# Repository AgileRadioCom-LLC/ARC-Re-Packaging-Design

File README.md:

# RPKG
Repo for ArcSynerCom RPKG Files
# ARC-Re-Packaging-Design

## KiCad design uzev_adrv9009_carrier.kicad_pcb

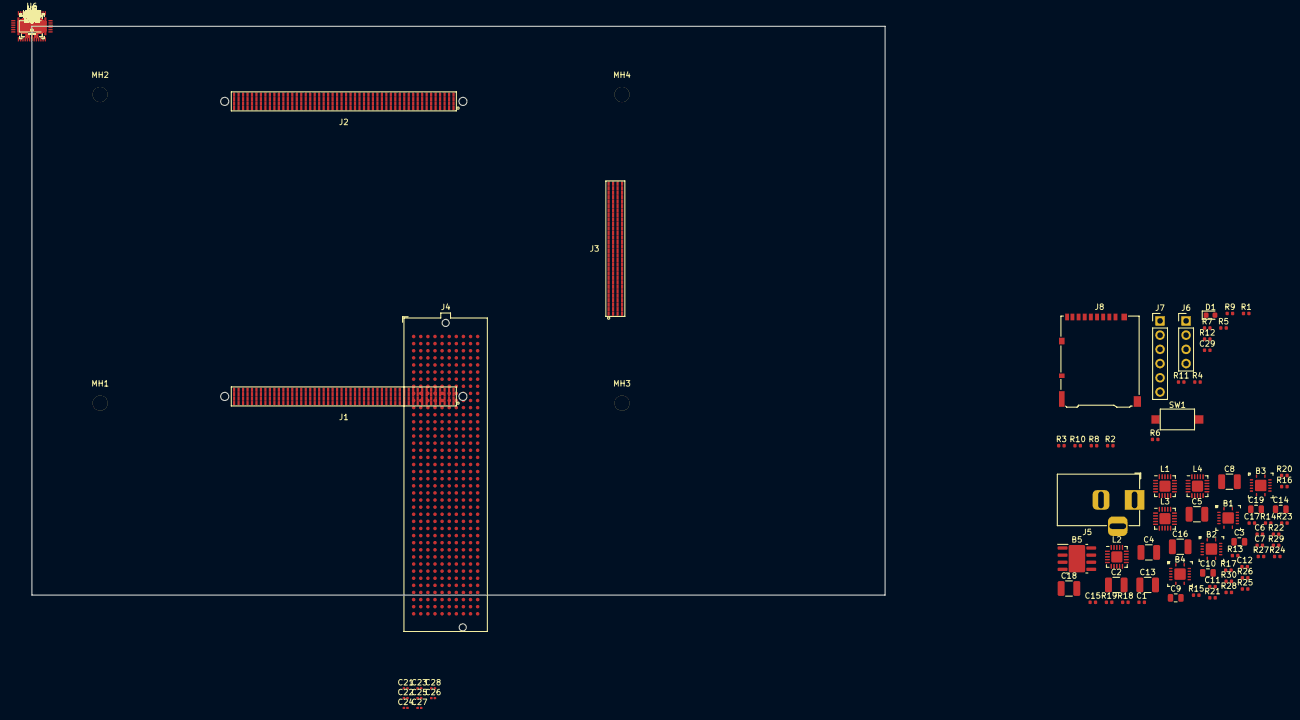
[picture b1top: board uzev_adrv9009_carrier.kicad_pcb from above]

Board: 8 copper layers, 152.4 x 101.6 mm, 179 parts (0 on the bottom side), 169 nets, no tracks yet.

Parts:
B1, B2, B3, B4, B6, B7: TPS54320; VQFN-14-1EP_3.5x3.5mm_P0.5mm_EP2.05x2.05mm
B5: TPS54531; SOIC-8-1EP_3.9x4.9mm_P1.27mm_EP2.95x4.9mm_Mask2.71x3.4mm
C1, C6, C7, C11, C12, C15, C17, C29, C40, C41, C42, C43, C44, C61, C66, C67, C68, C69, C75, C76: 100nF; C_0402_1005Metric
C2, C8, C13, C16, C18, C65, C70, C77: 47uF; C_1210_3225Metric
C3, C9, C14, C19, C60, C62, C71, C78: 10uF; C_0805_2012Metric
C4, C5: 33uF; C_1210_3225Metric
C10: 4.7uF; C_0805_2012Metric
C21, C22, C23, C24, C25, C26, C27, C28: 100nF; C_0201_0603Metric
C45, C46, C47, C48, C72, C79: 15nF; C_0402_1005Metric
C49: 2200pF; C_0402_1005Metric
C50, C51, C52, C53, C63, C64, C73, C80: 330pF; C_0402_1005Metric
C54: 22pF; C_0402_1005Metric
C55, C56, C57, C58, C59, C74, C81: 10nF; C_0402_1005Metric
D1: GREEN; LED_0603_1608Metric
D2: CDBC540-G; D_SOD-123
FB1: "120R@100MHz 0603"; L_0603_1608Metric
IND1, IND2, IND3, IND4, IND5, IND6, IND7: 4.7uH; L_1210_3225Metric
J1, J2: SEAF-40-05.0-S-10-2-A-K-TR_200P
J3: SEAF-30-05.0-S-10-2-A-K-TR_120P
J4: FMC_HPC_ADRV9009; Samtec_FMC_ASP-134602-01_10x40_P1.27mm_Vertical
J5: 12V_DC_IN; BarrelJack_Horizontal
J6: UART_HDR; PinHeader_1x04_P2.54mm_Vertical
J7: JTAG_HDR; PinHeader_1x06_P2.54mm_Vertical
J8: MICRO_SD_DNP; microSD_HC_Hirose_DM3AT-SF-PEJM5
L1, L2, L3, L4, L5, L6: TPS7A85; QFN-20-1EP_3.5x3.5mm_P0.5mm_EP2x2mm
MH1, MH2, MH3, MH4: MountingHole_2.7mm
R1, R2: 2.2k; R_0402_1005Metric
R3, R10, R12, R46, R47, R48, R49: 10k; R_0402_1005Metric
R4, R5, R6, R7, R8, R9: 0R_DNP; R_0402_1005Metric
R11: 1k; R_0402_1005Metric
R13: 88.7k; R_0402_1005Metric
R14, R16, R18, R20, R22, R24, R26, R28, R30, R36, R37, R38, R39, R44, R50, R51, R52, R53, R55, R57, R59, R60, R62, R64, R66, R67, R68, R69, R70, R71: 100k; R_0402_1005Metric
R15, R27, R29, R63: 124k; R_0402_1005Metric
R17, R19: 215k; R_0402_1005Metric
R21: 316k; R_0402_1005Metric
R23: 12.4k; R_0402_1005Metric
R25: 49.9k; R_0402_1005Metric
R31, R32, R33, R34, R58, R65: 1.78k; R_0402_1005Metric
R35: 37.4k; R_0402_1005Metric
R40: 91k; R_0402_1005Metric
R41: 11k; R_0402_1005Metric
R42: 82k; R_0402_1005Metric
R43: 20k; R_0402_1005Metric
R45: 4.7k; R_0402_1005Metric
R54: 61.9k; R_0402_1005Metric
R56: 6.19k; R_0402_1005Metric
R61: 162k; R_0402_1005Metric
SW1: RESET; SW_SPST_CK_RS282G05A3
U6: TPS25730D; WQFN-38_TPS25730D
U7: TPS7A1633; HVSSOP-8_TPS7A1633

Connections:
/Power/B6_PG: B6.5, L5.4, R60.2
/Power/B7_PG: B7.5, L6.4, R67.2
/Power/CC1: C63.1, J5.3, U6.28
/Power/CC2: C64.1, R42.2, R43.1, U6.5, U6.29
/Power/L1_PG: B2.4, L1.5, R68.2
/Power/L2_PG: B3.4, B4.4, B5.4, L2.5, R69.2
/Power/L5_PG: B7.4, L5.5, R70.2
/Power/L6_PG: B1.4, L6.5, R71.2
/Power/LDO_1V5: U6.3, U6.4
/Power/LDO_3V3: R40.1, R42.1, R44.1, R44.2, R45.1, R49.1, U6.1, U6.7
/Power/VIN_3V3: C62.1, C67.1, U6.38, U7.7, U7.8
FMC_3P3V: B5.3, IND5.1, J4.C39, J4.D36, J4.D38, J4.D40, R21.1
FMC_A02_DP1_M2C_P: J2.A21, J4.A2
FMC_A03_DP1_M2C_N: J2.A22, J4.A3
FMC_A06_DP2_M2C_P: J2.C21, J4.A6
FMC_A07_DP2_M2C_N: J2.C22, J4.A7
FMC_A10_DP3_M2C_P: J2.A24, J4.A10
FMC_A11_DP3_M2C_N: J2.A25, J4.A11
FMC_A22_DP1_C2M_P: J2.D20, J4.A22
FMC_A23_DP1_C2M_N: J2.D21, J4.A23
FMC_A26_DP2_C2M_P: J2.B20, J4.A26
FMC_A27_DP2_C2M_N: J2.B21, J4.A27
FMC_A30_DP3_C2M_P: J2.B23, J4.A30
FMC_A31_DP3_C2M_N: J2.B24, J4.A31
FMC_B20_GBTCLK1_M2C_P: J2.C27, J4.B20
FMC_B21_GBTCLK1_M2C_N: J2.C28, J4.B21
FMC_C02_DP0_C2M_P: J2.D23, J4.C2
FMC_C03_DP0_C2M_N: J2.D24, J4.C3
FMC_C06_DP0_M2C_P: J2.C24, J4.C6
FMC_C07_DP0_M2C_N: J2.C25, J4.C7
FMC_C10_LA06_P: J1.D42, J4.C10
FMC_C11_LA06_N: J1.D43, J4.C11
FMC_C18_LA14_P: J1.C41, J4.C18
FMC_C19_LA14_N: J1.C42, J4.C19
FMC_C22_LA18_CC_P: J1.A27, J4.C22
FMC_C23_LA18_CC_N: J1.A28, J4.C23
FMC_D04_GBTCLK0_M2C_P: J2.D26, J4.D4
FMC_D05_GBTCLK0_M2C_N: J2.D27, J4.D5
FMC_D08_LA01_CC_P: J1.D32, J4.D8
FMC_D09_LA01_CC_N: J1.D33, J4.D9
FMC_D14_LA09_P: J1.D36, J4.D14
FMC_D15_LA09_N: J1.D37, J4.D15
FMC_D17_LA13_P: J1.A31, J4.D17
FMC_D18_LA13_N: J1.A32, J4.D18
FMC_D26_LA26_P: J1.A41, J4.D26
FMC_D27_LA26_N: J1.A42, J4.D27
FMC_G06_LA00_CC_P: J1.C31, J4.G6
FMC_G07_LA00_CC_N: J1.C32, J4.G7
FMC_G09_LA03_P: J1.B42, J4.G9
FMC_G10_LA03_N: J1.B43, J4.G10
FMC_G12_LA08_P: J1.D39, J4.G12
FMC_G15_LA12_P: J1.C35, J4.G15
FMC_G16_LA12_N: J1.C36, J4.G16
FMC_G18_LA16_P: J1.C27, J4.G18
FMC_G19_LA16_N: J1.C28, J4.G19
FMC_G21_LA20_P: J1.D25, J4.G21
FMC_G22_LA20_N: J1.D26, J4.G22
FMC_G24_LA22_P: J1.C38, J4.G24
FMC_G25_LA22_N: J1.C39, J4.G25
FMC_G27_LA25_P: J1.B25, J4.G27
FMC_G28_LA25_N: J1.B26, J4.G28
FMC_H07_LA02_P: J1.B28, J4.H7
FMC_H08_LA02_N: J1.B29, J4.H8
FMC_H10_LA04_P: J1.A35, J4.H10
FMC_H11_LA04_N: J1.A36, J4.H11
FMC_H13_LA07_P: J1.B32, J4.H13
FMC_H14_LA07_N: J1.B33, J4.H14
FMC_H16_LA11_P: J1.A38, J4.H16
FMC_H17_LA11_N: J1.A39, J4.H17
FMC_H19_LA15_P: J1.D28, J4.H19
FMC_H20_LA15_N: J1.D29, J4.H20
FMC_H22_LA19_P: J1.C24, J4.H22
FMC_H23_LA19_N: J1.C25, J4.H23
FMC_H25_LA21_P: J1.A24, J4.H25
FMC_H26_LA21_N: J1.A25, J4.H26
GND: B1.2, B2.2, B3.2, B4.2, B5.2, B5.6, B6.2, B7.2, C10.2, C11.2, C45.2, C46.2, C47.2, C48.2, C49.2, C50.2, C51.2, C52.2, C53.2, C54.2, C55.2, C56.2, C57.2, C58.2, C59.2, C60.2, C61.2, C62.2, C63.2, C64.2, C65.2, C66.2, C67.2, C68.2, C70.2, C71.2, C72.2, C73.2, C74.2, C75.2, C77.2, C78.2, C79.2, C80.2, C81.2, D2.2, J5.2, J6.4, J7.6, J8.6, J8.11, L1.2, L2.2, L3.2, L4.2, L5.2, L5.6, L6.2, L6.6, R14.2, R16.2, R18.2, R20.2, R21.2, R22.1, R22.2, R24.2, R26.2, R28.2, R30.2, R36.2, R37.2, R38.2, R39.2, R41.2, R43.2, R45.2, R46.1, R47.1, R48.1, R55.2, R56.2, R57.1, R57.2, R59.2, R62.2, R63.2, R64.1, R64.2, R66.2, SW1.2, U6.8, U6.9, U6.11, U6.12, U6.14, U6.16, U6.17, U6.31, U6.34, U6.35, U6.39, U7.2, U7.9
JTAG_TCK: J1.D1, R6.1
JTAG_TDI: J1.C2, R7.1
JTAG_TDO: J1.D2, R8.1
JTAG_TMS: J1.C1, R9.1
MGTAVCC: J2.C1, J2.C2, J2.D4, J2.D7, J2.D10, J2.D13, L1.3, R23.1
MGTAVTT: J2.A1, J2.A2, J2.B4, J2.B7, J2.B10, J2.B13, L2.3, R25.1
MGTRAVCC: C71.1, J3.B29, L5.3
MGTRAVCC_SENSE: J3.D20, R56.1
MGTRAVTT: C78.1, J3.B25, L6.3
MGTRAVTT_SENSE: J3.C25, R63.1
MGTVCCAUX: C10.1, C11.1, FB1.2, J2.A5, J2.A8
unnamed: B1.3, IND1.1, L1.1, R13.1, R50.1
unnamed: B1.5, L1.4, R50.2
unnamed: B1.6, R13.2, R14.1
unnamed: B1.7, C40.2, IND1.2
unnamed: B1.8, C40.1
unnamed: B1.9, C50.1, R31.1
unnamed: B1.10, R36.1
unnamed: B1.11, C55.1
unnamed: B2.3, IND2.1, L2.1, R15.1, R51.1
unnamed: B2.5, L2.4, R51.2
unnamed: B2.6, R15.2, R16.1
unnamed: B2.7, C41.2, IND2.2
unnamed: B2.8, C41.1
unnamed: B2.9, C51.1, R32.1
unnamed: B2.10, R37.1
unnamed: B2.11, C56.1
unnamed: B3.3, IND3.1, L3.1, R17.1, R52.1
unnamed: B3.5, L3.4, R52.2
unnamed: B3.6, R17.2, R18.1
unnamed: B3.7, C42.2, IND3.2
unnamed: B3.8, C42.1
unnamed: B3.9, C52.1, R33.1
unnamed: B3.10, R38.1
unnamed: B3.11, C57.1
unnamed: B4.3, IND4.1, L4.1, R19.1, R53.1
unnamed: B4.5, L4.4, R53.2
unnamed: B4.6, R19.2, R20.1
unnamed: B4.7, C43.2, IND4.2
unnamed: B4.8, C43.1
unnamed: B4.9, C53.1, R34.1
unnamed: B4.10, R39.1
unnamed: B4.11, C58.1
unnamed: B5.7, C44.2, D2.1, IND5.2
unnamed: B5.8, C44.1
unnamed: B5.9, C54.1, R35.1
unnamed: B6.3, C70.1, IND6.1, L5.1, R54.1, R60.1
unnamed: B6.6, R54.2, R55.1
unnamed: B6.7, C69.2, IND6.2
unnamed: B6.8, C69.1
unnamed: B6.9, C73.1, R58.1
unnamed: B6.10, R59.1
unnamed: B6.11, C74.1
unnamed: B7.3, C77.1, IND7.1, L6.1, R61.1, R67.1
unnamed: B7.6, R61.2, R62.1
unnamed: B7.7, C76.2, IND7.2
unnamed: B7.8, C76.1
unnamed: B7.9, C80.1, R65.1
unnamed: B7.10, R66.1
unnamed: B7.11, C81.1
unnamed: C45.1, R31.2
unnamed: C46.1, R32.2
unnamed: C47.1, R33.2
unnamed: C48.1, R34.2
unnamed: C49.1, R35.2
unnamed: C61.1, U7.5
unnamed: C72.1, R58.2
unnamed: C79.1, R65.2
unnamed: J7.2, R9.2
unnamed: J7.3, R6.2
unnamed: J7.4, R8.2
unnamed: J7.5, R7.2
unnamed: L1.6, R23.2, R24.1
unnamed: L2.6, R25.2, R26.1
unnamed: L3.6, R27.2, R28.1
unnamed: L4.6, R29.2, R30.1
unnamed: R4.2, R5.1
unnamed: R40.2, R41.1, U6.2
unnamed: R46.2, U6.26
unnamed: R47.2, U6.27
unnamed: R48.2, U6.36
unnamed: R49.2, U6.18
SD1_CD_N: J3.A23, J8.10
SD1_CLK: J3.B24, J8.5
SD1_CMD: J3.A25, J8.3
SD1_D0: J3.B26, J8.7
SD1_D1: J3.A27, J8.8
SD1_D2: J3.B28, J8.1
SD1_D3: J3.A29, J8.2
SOM_PG_OUT: B6.4, J1.D47
VADJ: FB1.1, J1.C3, J1.D3, J1.D4, J4.E39, J4.F40, J4.G39, J4.H40, J7.1, L3.3, R27.1
VCCO_HP_64: J1.A3, J1.B3, J1.B4, L4.3, R29.1
VIN: B1.1, B2.1, B3.1, B4.1, B5.1, B6.1, B7.1, C60.1, C65.1, C66.1, C68.1, C75.1, J1.A43, J1.A46, J1.A49, J1.A50, J1.B44, J1.B47, J1.B50, J1.C50, J5.1, R68.1, R69.1, R70.1, R71.1, U6.15, U6.20, U6.21, U6.22, U6.23, U6.24, U6.25, U6.30, U6.32, U6.33, U6.40, U7.1, U7.3

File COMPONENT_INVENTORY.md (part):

# UZEV Carrier — Component Inventory with Purpose

Total real components: 150

Purpose marked "CONFIRM" = not pinned by DEC log/datasheet; needs design-intent confirmation before third-party sign-off.

| Ref | Value | Footprint | Sheet | Purpose |
|---|---|---|---|---|
| B1 | TPS54320 | VQFN-14-1EP_3.5x3.5mm_P0.5mm_EP2.05x2.05mm | power | Buck regulator block — 12V→intermediate rail |
| B2 | TPS54320 | VQFN-14-1EP_3.5x3.5mm_P0.5mm_EP2.05x2.05mm | power | Buck regulator block — 12V→intermediate rail |
| B3 | TPS54320 | VQFN-14-1EP_3.5x3.5mm_P0.5mm_EP2.05x2.05mm | power | Buck regulator block — 12V→intermediate rail |
| B4 | TPS54320 | VQFN-14-1EP_3.5x3.5mm_P0.5mm_EP2.05x2.05mm | power | Buck regulator block — 12V→intermediate rail |
| B5 | TPS54531 | SOIC-8-1EP_3.9x4.9mm_P1.27mm_EP2.95x4.9mm_Mask2.71x3.4mm | power | Buck regulator block — 12V→intermediate rail |
| C1 | 100nF | C_0402_1005Metric | power | Decoupling cap (inferred — CONFIRM net/IC) |
| C2 | 47uF | C_1210_3225Metric | power | Bulk cap (inferred — CONFIRM rail) |
| C3 | 10uF | C_0805_2012Metric | power | Bulk cap (inferred — CONFIRM rail) |
| C4 | 33uF | C_1210_3225Metric | power | Capacitor (inferred — CONFIRM) |
| C5 | 33uF | C_1210_3225Metric | power | Capacitor (inferred — CONFIRM) |
| C6 | 100nF | C_0402_1005Metric | power | Decoupling cap (inferred — CONFIRM net/IC) |
| C7 | 100nF | C_0402_1005Metric | power | Decoupling cap (inferred — CONFIRM net/IC) |
| C8 | 47uF | C_1210_3225Metric | power | Bulk cap (inferred — CONFIRM rail) |
| C9 | 10uF | C_0805_2012Metric | power | Bulk cap (inferred — CONFIRM rail) |
| C10 | 4.7uF | C_0805_2012Metric | power | Capacitor (inferred — CONFIRM) |
| C11 | 100nF | C_0402_1005Metric | power | Decoupling cap (inferred — CONFIRM net/IC) |
| C12 | 100nF | C_0402_1005Metric | power | Decoupling cap (inferred — CONFIRM net/IC) |
| C13 | 47uF | C_1210_3225Metric | power | Bulk cap (inferred — CONFIRM rail) |
| C14 | 10uF | C_0805_2012Metric | power | Bulk cap (inferred — CONFIRM rail) |
| C15 | 100nF | C_0402_1005Metric | power | Decoupling cap (inferred — CONFIRM net/IC) |
| C16 | 47uF | C_1210_3225Metric | power | Bulk cap (inferred — CONFIRM rail) |
| C17 | 100nF | C_0402_1005Metric | power | Decoupling cap (inferred — CONFIRM net/IC) |
| C18 | 47uF | C_1210_3225Metric | power | Bulk cap (inferred — CONFIRM rail) |
| C19 | 10uF | C_0805_2012Metric | power | Bulk cap (inferred — CONFIRM rail) |
| C21 | 100nF | C_0201_0603Metric | adrv9009_signals | Decoupling cap (inferred — CONFIRM net/IC) |
| C22 | 100nF | C_0201_0603Metric | adrv9009_signals | Decoupling cap (inferred — CONFIRM net/IC) |
| C23 | 100nF | C_0201_0603Metric | adrv9009_signals | Decoupling cap (inferred — CONFIRM net/IC) |
| C24 | 100nF | C_0201_0603Metric | adrv9009_signals | Decoupling cap (inferred — CONFIRM net/IC) |
| C25 | 100nF | C_0201_0603Metric | adrv9009_signals | Decoupling cap (inferred — CONFIRM net/IC) |
| C26 | 100nF | C_0201_0603Metric | adrv9009_signals | Decoupling cap (inferred — CONFIRM net/IC) |
| C27 | 100nF | C_0201_0603Metric | adrv9009_signals | Decoupling cap (inferred — CONFIRM net/IC) |
| C28 | 100nF | C_0201_0603Metric | adrv9009_signals | Decoupling cap (inferred — CONFIRM net/IC) |
| C29 | 100nF | C_0402_1005Metric | support_io | Decoupling cap (inferred — CONFIRM net/IC) |
| C40 | 100nF | C_0402_1005Metric | power | Decoupling cap (inferred — CONFIRM net/IC) |
| C41 | 100nF | C_0402_1005Metric | power | Decoupling cap (inferred — CONFIRM net/IC) |
| C42 | 100nF | C_0402_1005Metric | power | Decoupling cap (inferred — CONFIRM net/IC) |
| C43 | 100nF | C_0402_1005Metric | power | Decoupling cap (inferred — CONFIRM net/IC) |
| C44 | 100nF | C_0402_1005Metric | power | Decoupling cap (inferred — CONFIRM net/IC) |
| C45 | 15nF | C_0402_1005Metric | power | Capacitor (inferred — CONFIRM) |
| C46 | 15nF | C_0402_1005Metric | power | Capacitor (inferred — CONFIRM) |
| C47 | 15nF | C_0402_1005Metric | power | Capacitor (inferred — CONFIRM) |
| C48 | 15nF | C_0402_1005Metric | power | Capacitor (inferred — CONFIRM) |
| C49 | 2200pF | C_0402_1005Metric | power | HF filter cap (inferred — CONFIRM net) |
| C50 | 330pF | C_0402_1005Metric | power | HF filter cap (inferred — CONFIRM net) |
| C51 | 330pF | C_0402_1005Metric | power | HF filter cap (inferred — CONFIRM net) |
| C52 | 330pF | C_0402_1005Metric | power | HF filter cap (inferred — CONFIRM net) |
| C53 | 330pF | C_0402_1005Metric | power | HF filter cap (inferred — CONFIRM net) |
| C54 | 22pF | C_0402_1005Metric | power | HF filter cap (inferred — CONFIRM net) |
| C55 | 10nF | C_0402_1005Metric | power | Capacitor (inferred — CONFIRM) |
| C56 | 10nF | C_0402_1005Metric | power | Capacitor (inferred — CONFIRM) |
| C57 | 10nF | C_0402_1005Metric | power | Capacitor (inferred — CONFIRM) |
| C58 | 10nF | C_0402_1005Metric | power | Capacitor (inferred — CONFIRM) |
| C59 | 10nF | C_0402_1005Metric | power | Capacitor (inferred — CONFIRM) |
| C60 | 10uF | C_0805_2012Metric | power | Bulk cap (inferred — CONFIRM rail) |
| C61 | 100nF | C_0402_1005Metric | power | Decoupling cap (inferred — CONFIRM net/IC) |
| C62 | 10uF | C_0805_2012Metric | power | Bulk cap (inferred — CONFIRM rail) |
| C63 | 330pF | C_0402_1005Metric | power | HF filter cap (inferred — CONFIRM net) |
| C64 | 330pF | C_0402_1005Metric | power | HF filter cap (inferred — CONFIRM net) |
| C65 | 47uF | C_1210_3225Metric | power | Bulk cap (inferred — CONFIRM rail) |
| C66 | 100nF | C_0402_1005Metric | power | Decoupling cap (inferred — CONFIRM net/IC) |
| C67 | 100nF | C_0402_1005Metric | power | Decoupling cap (inferred — CONFIRM net/IC) |
| D1 | GREEN | LED_0603_1608Metric | support_io | Diode (confirm: protection/indicator) |
| D2 | CDBC540-G | D_SOD-123 | power | Diode (confirm: protection/indicator) |
| IND1 | 4.7uH | L_1210_3225Metric | power | CONFIRM |
| IND2 | 4.7uH | L_1210_3225Metric | power | CONFIRM |
| IND3 | 4.7uH | L_1210_3225Metric | power | CONFIRM |
| IND4 | 4.7uH | L_1210_3225Metric | power | CONFIRM |
| IND5 | 4.7uH | L_1210_3225Metric | power | CONFIRM |
| J1 | JX1 | SEAF-40-05.0-S-10-2-A-K-TR_200P | connectors | Connector (confirm: SOM/FMC/JTAG/SD) |
| J1 | JX1 | SEAF-40-05.0-S-10-2-A-K-TR_200P | connectors | Connector (confirm: SOM/FMC/JTAG/SD) |
| J1 | JX1 | SEAF-40-05.0-S-10-2-A-K-TR_200P | connectors | Connector (confirm: SOM/FMC/JTAG/SD) |
| J1 | JX1 | SEAF-40-05.0-S-10-2-A-K-TR_200P | connectors | Connector (confirm: SOM/FMC/JTAG/SD) |
| J2 | JX2 | SEAF-40-05.0-S-10-2-A-K-TR_200P | connectors | Connector (confirm: SOM/FMC/JTAG/SD) |
| J2 | JX2 | SEAF-40-05.0-S-10-2-A-K-TR_200P | connectors | Connector (confirm: SOM/FMC/JTAG/SD) |
| J2 | JX2 | SEAF-40-05.0-S-10-2-A-K-TR_200P | connectors | Connector (confirm: SOM/FMC/JTAG/SD) |
| J2 | JX2 | SEAF-40-05.0-S-10-2-A-K-TR_200P | connectors | Connector (confirm: SOM/FMC/JTAG/SD) |
| J3 | JX3 | SEAF-30-05.0-S-10-2-A-K-TR_120P | connectors | Connector (confirm: SOM/FMC/JTAG/SD) |
| J3 | JX3 | SEAF-30-05.0-S-10-2-A-K-TR_120P | connectors | Connector (confirm: SOM/FMC/JTAG/SD) |
| J3 | JX3 | SEAF-30-05.0-S-10-2-A-K-TR_120P | connectors | Connector (confirm: SOM/FMC/JTAG/SD) |
| J3 | JX3 | SEAF-30-05.0-S-10-2-A-K-TR_120P | connectors | Connector (confirm: SOM/FMC/JTAG/SD) |
| J4 | FMC_HPC_ADRV9009 | Samtec_FMC_ASP-134602-01_10x40_P1.27mm_Vertical | connectors | Connector (confirm: SOM/FMC/JTAG/SD) |
| J4 | FMC_HPC_ADRV9009 | Samtec_FMC_ASP-134602-01_10x40_P1.27mm_Vertical | connectors | Connector (confirm: SOM/FMC/JTAG/SD) |
| J4 | FMC_HPC_ADRV9009 | Samtec_FMC_ASP-134602-01_10x40_P1.27mm_Vertical | connectors | Connector (confirm: SOM/FMC/JTAG/SD) |
| J4 | FMC_HPC_ADRV9009 | Samtec_FMC_ASP-134602-01_10x40_P1.27mm_Vertical | connectors | Connector (confirm: SOM/FMC/JTAG/SD) |
| J4 | FMC_HPC_ADRV9009 | Samtec_FMC_ASP-134602-01_10x40_P1.27mm_Vertical | connectors | Connector (confirm: SOM/FMC/JTAG/SD) |
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
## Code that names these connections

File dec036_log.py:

#!/usr/bin/env python3
"""DEC-036: Append log entry to DECISIONS_LOG.md (atomic write)."""
import os, hashlib

PROJ = os.path.dirname(os.path.abspath(__file__))
LOG  = os.path.join(PROJ, 'DECISIONS_LOG.md')

PRE_MD5 = '44b2e47d94f8146dea389bb87f769320'
actual = hashlib.md5(open(LOG, 'rb').read()).hexdigest()
if actual != PRE_MD5:
    print(f'PRE-CHECK FAILED: md5={actual} expected={PRE_MD5}')
    import sys; sys.exit(1)

ENTRY = """

## 2026-05-29 — DEC-036 — Replace HUSB238 with TPS25730D USB-C PD sink + TPS7A1633 bootstrap LDO

**Status:** APPLIED

**Decision:** Remove HUSB238 (Hynetek, Chinese-made) from DEC-035 USB-C PD input section.
Replace with TPS25730D (Texas Instruments, US) + TPS7A1633 (TI) bootstrap LDO.

**Rationale:** Defense UAV supply chain requires US-made components. HUSB238 is manufactured by
Hynetek Semiconductor (Shenzhen, China). TPS25730D is a TI product (Dallas, TX, USA) with
equivalent or superior functionality: integrated PPHV power switch (no external PMOS needed),
hardware-only ADCINx strap configuration, 7A continuous / 10A pulsed VBUS sink capability.

**TPS25730D configuration (verified vs SLVSGP9, Table 8-x):**
- ADCIN1 (pin 2): 91kΩ/11kΩ divider from LDO_3V3 → value=2 → PDO min = 12V
- ADCIN2 (pin 3): wire to LDO_1V5 (pin 4) → value=5 → PDO max = 15V (Table 8-1 shortcut)
- ADCIN3 (pin 5): 82kΩ/20kΩ divider → value=3 → operating current = 3A
- ADCIN4 (pin 7): 100kΩ/4.7kΩ divider → value=1 → max current = 3A
- RESERVED (pins 26,27,36): 10kΩ each to GND per datasheet Table 5-1
- FAULT_IN (pin 18): 10kΩ pullup to LDO_3V3 (maintains connection on VBUS loss)
- CC1/CC2 (pins 28,29): 330pF filter caps to GND

**TPS7A1633 bootstrap LDO (verified vs SBVS171F):**
- Required because TPS25730D VIN_3V3 (pin 38) must be driven before PD negotiation begins.
  Without external VIN_3V3, ADCIN2=5 config means "USB PD disabled until I2C load" — dead-battery mode.
  TPS7A1633 (60V-in, 3.3V fixed, 100mA, HVSSOP-8) driven from VBUS provides VIN_3V3 at power-on,
  bypassing dead-battery mode so hardware ADCINx straps are read immediately.
- IN: VBUS rail. OUT: VIN_3V3 net → TPS25730D pin 38.
- EN: tied to IN (always-on while VBUS present).
- DELAY: 100nF cap to GND.
- DNC (pin 4): left open.

**Footprint sources:**
- TPS25730D: WQFN-38 REF0038A, 5.90×3.90mm, 0.4mm pitch (SLVSGP9 packaging chapter)
- TPS7A1633: HVSSOP-8 DDC, 3.0×3.0mm, 0.65mm pitch (SBVS171F)
- USB4135-GF-A: corrected per GCT Drawing USB4135 Rev A2 13/09/24 (6 signal pads only;
  prior footprint incorrectly included D+/D-/SBU1/SBU2 pads which do not exist on power-only connector)

**Files modified:**
- `DECISIONS_LOG.md`: this entry
- `UZEV_Connectors.lib`: removed HUSB238 symbol; updated USB_C_Receptacle (remove D+/D-/SBU pins);
  added TPS25730D (38-pin + 2 thermal) and TPS7A1633 (7-pin + thermal) symbols
- `UZEV_Connectors.pretty/SOT-23-9_Hynetek_HUSB238.kicad_mod`: deleted
- `UZEV_Connectors.pretty/USB_C_Receptacle_GCT_USB4135.kicad_mod`: corrected pad layout
  (6 signal pads per GCT drawing: VBUS×2, GND×2, CC1, CC2; 4 shell tabs)
- `UZEV_Connectors.pretty/WQFN-38_TPS25730D.kicad_mod`: added
- `UZEV_Connectors.pretty/HVSSOP-8_TPS7A1633.kicad_mod`: added
- `power.sch`: removed HUSB238 circuit (U6/C60/C61/R40/#PWR062-066 + wires/junctions/noconns);
  added TPS25730D (U6) + TPS7A1633 (U7) + all passives
- `phase7_prepcb_audit.py`: EXPECTED_HASHES updated

**Bitstream impact:** None (schematic-level change only).
"""

content = open(LOG).read()
new_content = content + ENTRY

tmp = LOG + '.tmp'
with open(tmp, 'w') as f:
    f.write(new_content)
os.replace(tmp, LOG)

post_md5 = hashlib.md5(open(LOG, 'rb').read()).hexdigest()
print(f'Done. post_md5={post_md5}  size={os.path.getsize(LOG)}')

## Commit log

2026-06-29 Add UZEV Carrier V5 project for migration
2026-06-29 Cleaned repository: removed temp files and initialized structure
2026-06-29 Initial commit of clean KiCad files
